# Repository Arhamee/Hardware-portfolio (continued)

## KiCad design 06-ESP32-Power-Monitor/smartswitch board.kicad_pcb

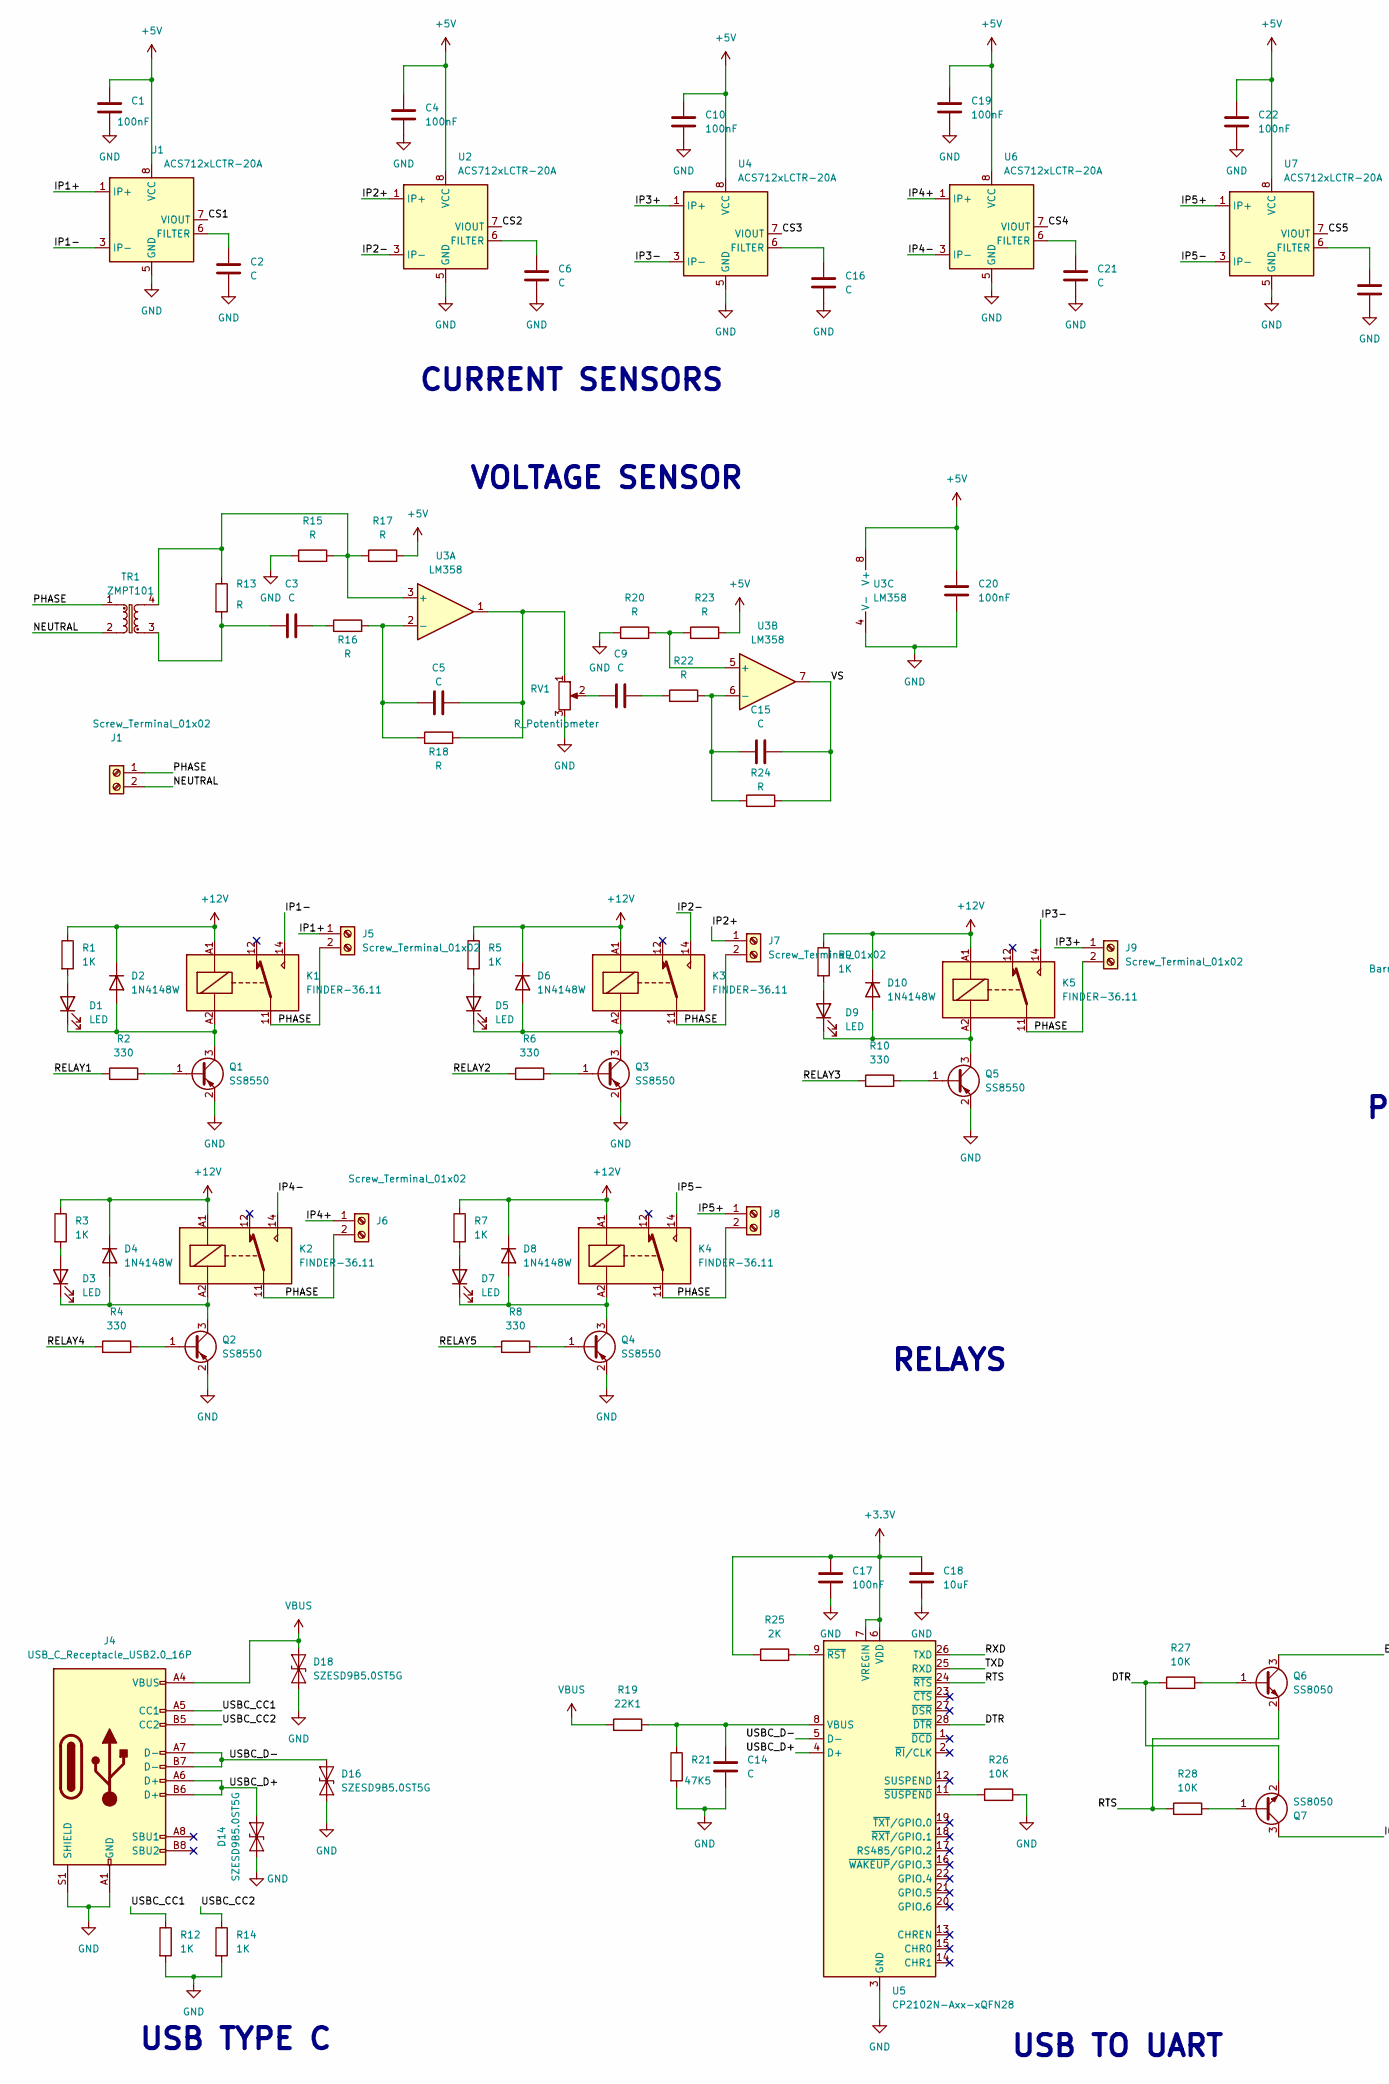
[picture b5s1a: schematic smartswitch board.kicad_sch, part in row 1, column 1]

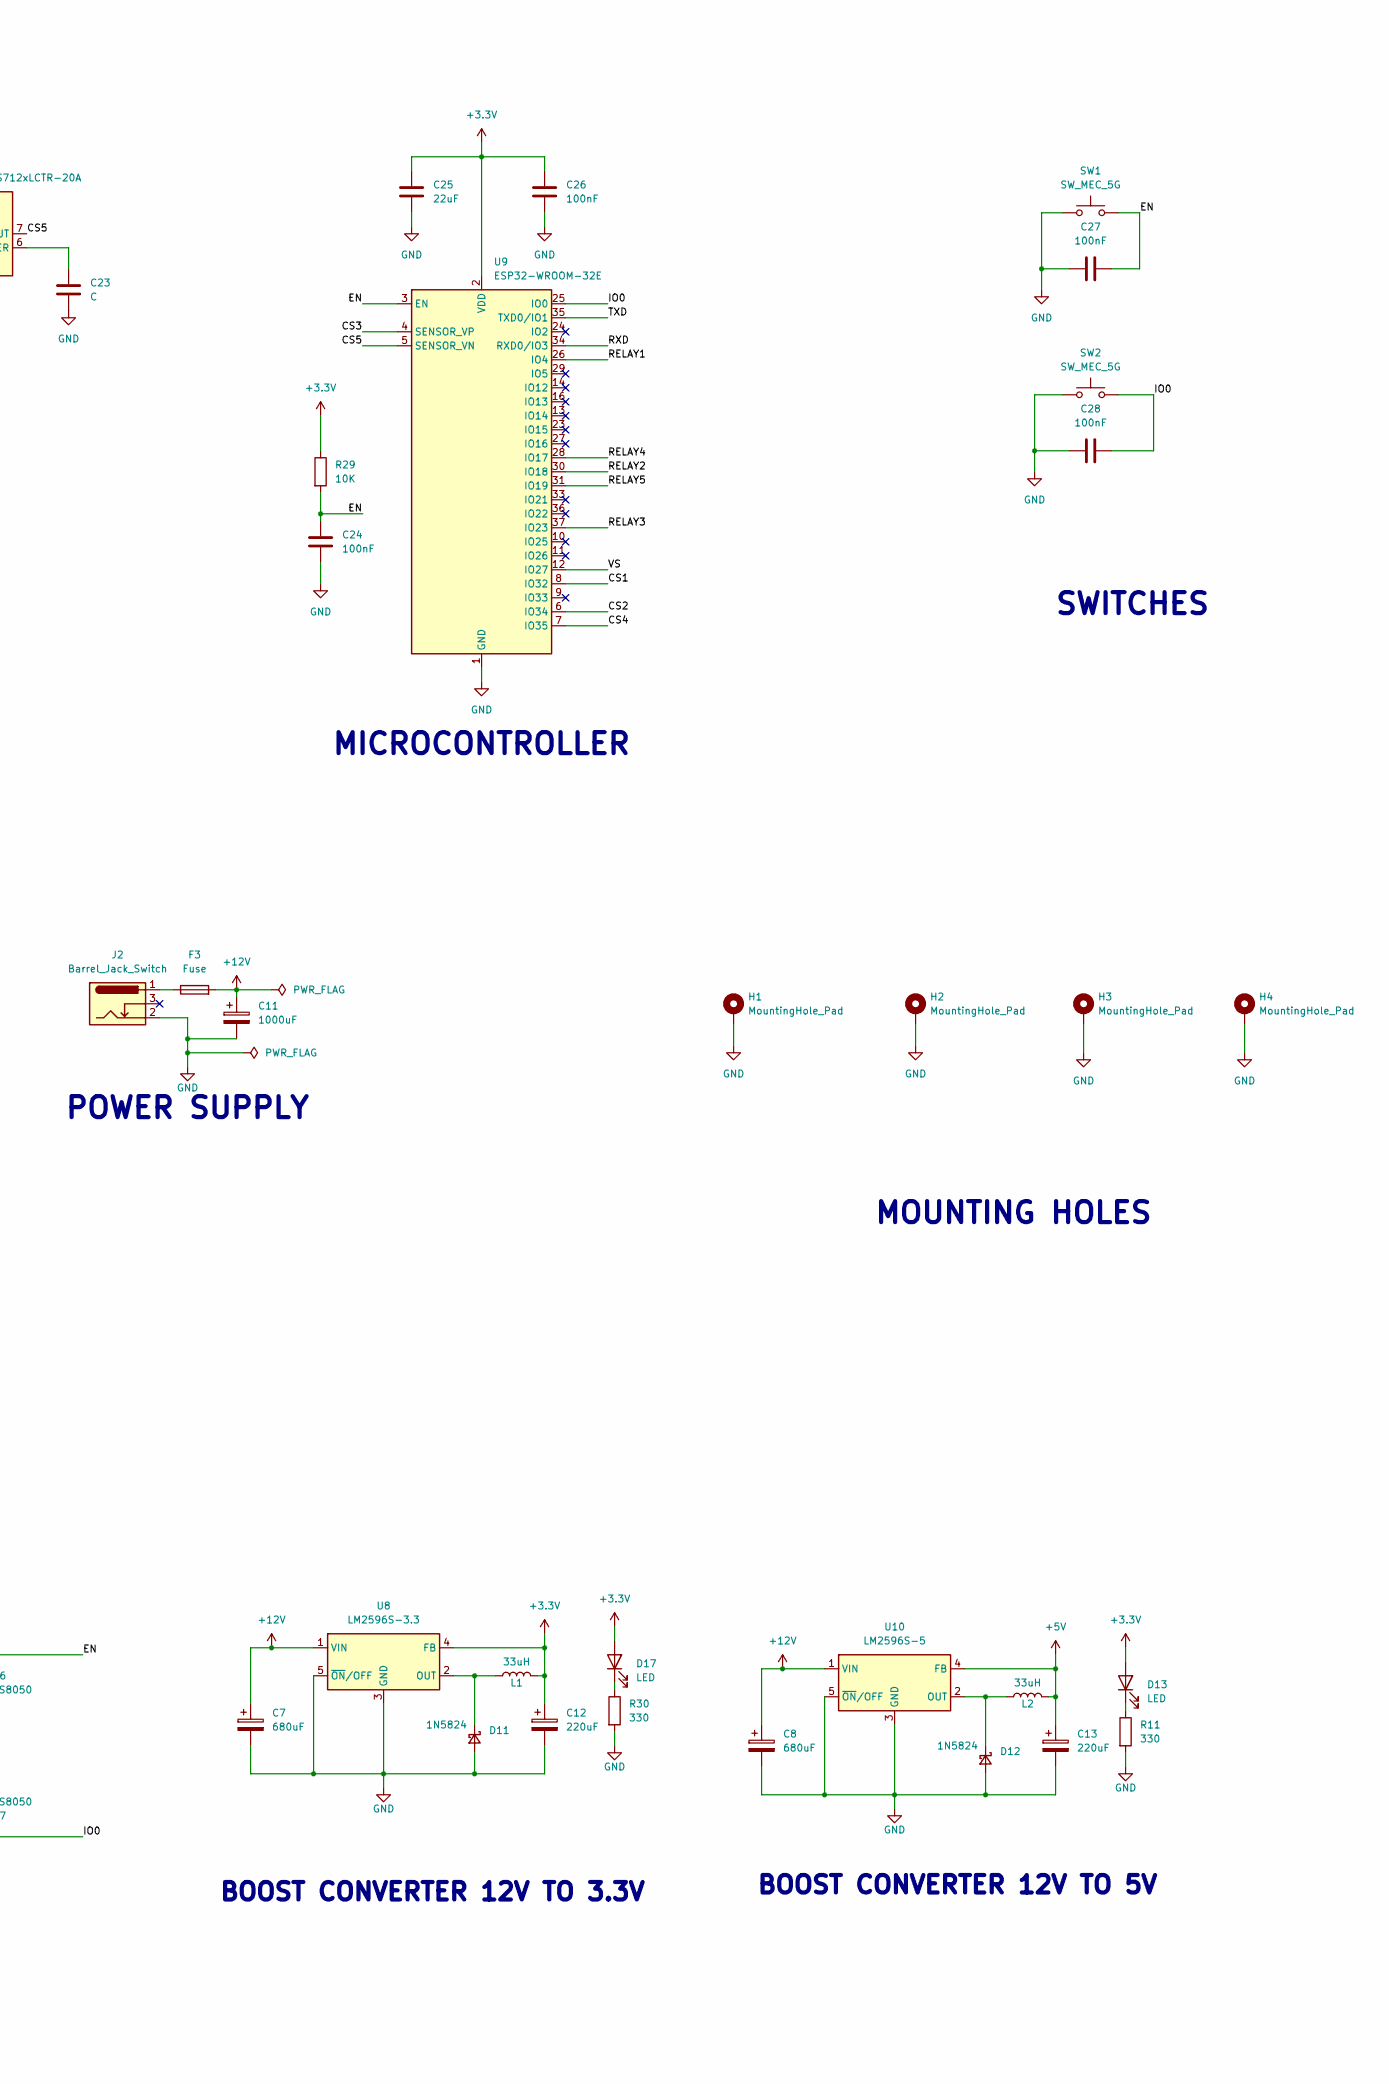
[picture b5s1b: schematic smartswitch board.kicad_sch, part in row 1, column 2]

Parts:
C1, C4, C10, C17, C19, C20, C22, C24, C26, C27, C28: 100nF; C_0402_1005Metric_Pad0.74x0.62mm_HandSolder
C2, C3, C5, C6, C9, C14, C15, C16, C23: C; C_0402_1005Metric_Pad0.74x0.62mm_HandSolder
C7, C8: 680uF; CP_Radial_D7.5mm_P2.50mm
C11: 1000uF; CP_Radial_D8.0mm_P3.50mm
C12, C13: 220uF; CP_Radial_D6.3mm_P2.50mm
C18: 10uF; C_0603_1608Metric_Pad1.08x0.95mm_HandSolder
C21: C; C_0603_1608Metric_Pad1.08x0.95mm_HandSolder
C25: 22uF; C_0603_1608Metric_Pad1.08x0.95mm_HandSolder
D1, D3, D5: LED; C_0402_1005Metric_Pad0.74x0.62mm_HandSolder
D2, D4, D6, D8, D10: 1N4148W; D_SOD-123
D7, D9, D13, D17: LED; LED_0402_1005Metric_Pad0.77x0.64mm_HandSolder
D11, D12: 1N5824; D_0603_1608Metric_Pad1.05x0.95mm_HandSolder
D14, D16, D18: SZESD9B5.0ST5G; D_SOD-923
F3: Fuse; Fuse_1210_3225Metric_Pad1.42x2.65mm_HandSolder
H1, H2, H3, H4: MountingHole_Pad; MountingHole_2.2mm_M2_DIN965_Pad
J1, J5, J6, J7, J8, J9: Screw_Terminal_01x02; TerminalBlock_Phoenix_MKDS-1,5-2_1x02_P5.00mm_Horizontal
J2: Barrel_Jack_Switch; BarrelJack_Horizontal
J4: USB_C_Receptacle_USB2.0_16P; USB_C_Receptacle_GCT_USB4105-xx-A_16P_TopMnt_Horizontal
K1, K2, K3, K4, K5: FINDER-36.11; Relay_SPDT_Finder_36.11
L1, L2: 33uH; L_Changjiang_FNR4015S
Q1, Q2, Q3, Q4, Q5: SS8550; SOT-23
Q6, Q7: SS8050; SOT-23
R1, R3, R5, R7, R9, R12, R14: 1K; R_0603_1608Metric_Pad0.98x0.95mm_HandSolder
R2, R4, R6, R8, R10, R11, R30: 330; R_0603_1608Metric_Pad0.98x0.95mm_HandSolder
R13, R15, R16, R17, R18, R20, R22, R23, R24: R; R_0603_1608Metric_Pad0.98x0.95mm_HandSolder
R19: 22K1; R_0603_1608Metric_Pad0.98x0.95mm_HandSolder
R21: 47K5; R_0603_1608Metric_Pad0.98x0.95mm_HandSolder
R25: 2K; R_0603_1608Metric_Pad0.98x0.95mm_HandSolder
R26, R27, R28, R29: 10K; R_0603_1608Metric_Pad0.98x0.95mm_HandSolder
RV1: R_Potentiometer; Potentiometer_Bourns_3296W_Vertical
SW1, SW2: SW_MEC_5G; PTS645S_SMTR92_CNK
TR1: ZMPT101; Transformer_Zeming_ZMPT101K
U1, U2, U4, U6, U7: ACS712xLCTR-20A; SOIC-8_3.9x4.9mm_P1.27mm
U3: LM358; SOIC-8_3.9x4.9mm_P1.27mm
U5: CP2102N-Axx-xQFN28; QFN-28-1EP_5x5mm_P0.5mm_EP3.35x3.35mm
U8: LM2596S-3.3; TO-263-5_TabPin3
U9: ESP32-WROOM-32E; ESP32-WROOM-32D
U10: LM2596S-5; TO-263-5_TabPin3

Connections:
+3.3V: C12.1, C17.1, C18.1, C25.1, C26.1, D13.2 (A), D17.2 (A), L1.2, R25.1, R29.1, U5.6 (VDD), U5.7 (VREGIN), U8.4 (FB), U9.2 (VDD)
+5V: C1.1, C4.1, C10.1, C13.1, C19.1, C20.2, C22.1, L2.2, R17.2, R23.2, U1.8 (VCC), U2.8 (VCC), U3.8 (V+), U4.8 (VCC), U6.8 (VCC), U7.8 (VCC), U10.4 (FB)
+12V: C7.1, C8.1, C11.1, D2.1 (K), D4.1 (K), D6.1 (K), D8.1 (K), D10.1 (K), F3.2, K1.A1, K2.A1, K3.A1, K4.A1, K5.A1, R1.1, R3.1, R5.1, R7.1, R9.1, U8.1 (VIN), U10.1 (VIN)
/CS1: U1.7 (VIOUT), U9.8 (IO32)
/CS2: U2.7 (VIOUT), U9.6 (IO34)
/CS3: U4.7 (VIOUT), U9.4 (SENSOR_VP)
/CS4: U6.7 (VIOUT), U9.7 (IO35)
/CS5: U7.7 (VIOUT), U9.5 (SENSOR_VN)
/DTR: Q7.2 (E), R27.1, U5.28 (~DTR)
/EN: C24.1, C27.1, Q6.3 (C), R29.2, SW1.3 (B), SW1.4 (B), U9.3 (EN)
/IO0: C28.2, Q7.3 (C), SW2.3 (B), SW2.4 (B), U9.25 (IO0)
/IP1+: J5.1, U1.1 (IP+), U1.2 (IP+)
/IP1-: K1.14, U1.3 (IP-), U1.4 (IP-)
/IP2+: J7.1, U2.1 (IP+), U2.2 (IP+)
/IP2-: K3.14, U2.3 (IP-), U2.4 (IP-)
/IP3+: J9.1, U4.1 (IP+), U4.2 (IP+)
/IP3-: K5.14, U4.3 (IP-), U4.4 (IP-)
/IP4+: J6.1, U6.1 (IP+), U6.2 (IP+)
/IP4-: K2.14, U6.3 (IP-), U6.4 (IP-)
/IP5+: J8.1, U7.1 (IP+), U7.2 (IP+)
/IP5-: K4.14, U7.3 (IP-), U7.4 (IP-)
/NEUTRAL: J1.2, TR1.2
/PHASE: J1.1, J5.2, J6.2, J7.2, J8.2, J9.2, K1.11, K2.11, K3.11, K4.11, K5.11, TR1.1
/RELAY1: R2.1, U9.26 (IO4)
/RELAY2: R6.1, U9.30 (IO18)
/RELAY3: R10.1, U9.37 (IO23)
/RELAY4: R4.1, U9.28 (IO17)
/RELAY5: R8.1, U9.31 (IO19)
/RTS: Q6.2 (E), R28.1, U5.24 (~RTS)
/RXD: U5.26 (TXD), U9.34 (RXD0/IO3)
/TXD: U5.25 (RXD), U9.35 (TXD0/IO1)
/USBC_CC1: J4.A5 (CC1), R12.1
/USBC_CC2: J4.B5 (CC2), R14.1
/USBC_D+: D14.2 (A2), J4.A6 (D+), J4.B6 (D+), U5.4 (D+)
/USBC_D-: D16.2 (A2), J4.A7 (D-), J4.B7 (D-), U5.5 (D-)
/VS: C15.2, R24.2, U3.7, U9.12 (IO27)
GND: C1.2, C2.2, C4.2, C6.2, C7.2, C8.2, C10.2, C11.2, C12.2, C13.2, C14.2, C16.2, C17.2, C18.2, C19.2, C20.1, C21.2, C22.2, C23.2, C24.2, C25.2, C26.2, C27.2, C28.1, D11.2 (A), D12.2 (A), D14.1 (A1), D16.1 (A1), D18.1 (A1), H1.1, H2.1, H3.1, H4.1, J2.2, J4.A1 (GND), J4.A12 (GND), J4.B1 (GND), J4.B12 (GND), J4.S1 (SHIELD), Q1.2 (E), Q2.2 (E), Q3.2 (E), Q4.2 (E), Q5.2 (E), R11.2, R12.2, R14.2, R15.1, R20.1, R21.2, R26.2, R30.2, RV1.3, SW1.1 (A), SW1.2 (A), SW2.1 (A), SW2.2 (A), U1.5 (GND), U2.5 (GND), U3.4 (V-), U4.5 (GND), U5.3 (GND), U5.29 (GND), U6.5 (GND), U7.5 (GND), U8.3 (GND), U8.5 (~ON/OFF), U9.1 (GND), U9.15 (GND), U9.38 (GND), U9.39 (GND), U10.3 (GND), U10.5 (~ON/OFF)
unnamed: C3.1, R13.2, TR1.3
unnamed: C3.2, R16.1
unnamed: C5.2, R18.2, RV1.1, U3.1
unnamed: C9.1, RV1.2
unnamed: C9.2, R22.1
unnamed: D1.2 (A), R1.2
unnamed: D1.1 (K), D2.2 (A), K1.A2, Q1.3 (C)
unnamed: D3.2 (A), R3.2
unnamed: D3.1 (K), D4.2 (A), K2.A2, Q2.3 (C)
unnamed: D5.2 (A), R5.2
unnamed: D5.1 (K), D6.2 (A), K3.A2, Q3.3 (C)
unnamed: D7.2 (A), R7.2
unnamed: D7.1 (K), D8.2 (A), K4.A2, Q4.3 (C)
unnamed: D9.2 (A), R9.2
unnamed: D9.1 (K), D10.2 (A), K5.A2, Q5.3 (C)
unnamed: D11.1 (K), L1.1, U8.2 (OUT)
unnamed: D12.1 (K), L2.1, U10.2 (OUT)
unnamed: D13.1 (K), R11.1
unnamed: D17.1 (K), R30.1
unnamed: F3.1, J2.1
unnamed: Q1.1 (B), R2.2
unnamed: Q2.1 (B), R4.2
unnamed: Q3.1 (B), R6.2
unnamed: Q4.1 (B), R8.2
unnamed: Q5.1 (B), R10.2
unnamed: Q6.1 (B), R27.2
unnamed: Q7.1 (B), R28.2
unnamed: C2.1, U1.6 (FILTER)
unnamed: C6.1, U2.6 (FILTER)
unnamed: R13.1, R15.2, R17.1, TR1.4, U3.3 (+)
unnamed: C5.1, R16.2, R18.1, U3.2 (-)
unnamed: R20.2, R23.1, U3.5 (+)
unnamed: C15.1, R22.2, R24.1, U3.6 (-)
unnamed: C16.1, U4.6 (FILTER)
unnamed: C14.1, R19.2, R21.1, U5.8 (VBUS)
unnamed: R25.2, U5.9 (~RST)
unnamed: R26.1, U5.11 (~SUSPEND)
unnamed: C21.1, U6.6 (FILTER)
unnamed: C23.1, U7.6 (FILTER)
VBUS: D18.2 (A2), J4.A4 (VBUS), J4.A9 (VBUS), J4.B4 (VBUS), J4.B9 (VBUS), R19.1

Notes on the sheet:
SWITCHES
USB TYPE C
USB TO UART
VOLTAGE SENSOR
POWER SUPPLY
CURRENT SENSORS
MICROCONTROLLER
RELAYS
BOOST CONVERTER 12V TO 3.3V
BOOST CONVERTER 12V TO 5V
MOUNTING HOLES

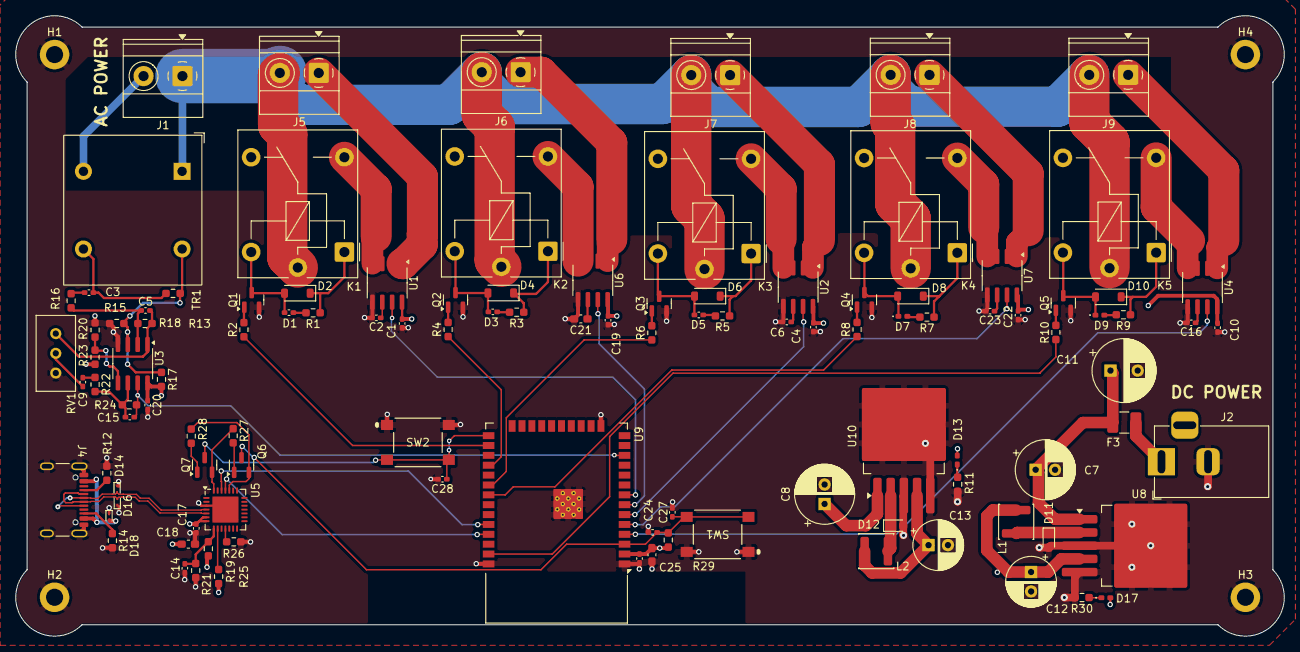
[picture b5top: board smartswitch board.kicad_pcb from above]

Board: 4 copper layers, 163.3 x 79.9 mm, 116 parts (0 on the bottom side), 77 nets.

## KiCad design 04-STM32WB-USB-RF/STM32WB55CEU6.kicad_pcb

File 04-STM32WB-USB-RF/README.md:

# STM32WB 4-Layer USB + RF Board

High-integrity 4-layer board combining USB 2.0 Full-Speed with 2.4 GHz RF,
built in KiCad 9.

**Status:** Design complete · DRC/ERC clean

## Stackup
| Layer | Purpose |
|---|---|
| 1 (Top) | Signal — components, USB D+/D−, RF traces |
| 2 | Solid ground plane |
| 3 | Second ground plane — low impedance, EMI shielding |
| 4 (Bottom) | 3.3V power plane, fed by single LDO |

The dual-ground stackup gives continuous return paths under high-speed traces,
reduces ground bounce and loop inductance, and sandwiches the power plane
between grounds.

## Features
- STM32WB dual-core (Cortex-M4 + Cortex-M0+)
- USB 2.0 FS with Type-C and ESD protection
- Impedance-controlled D+/D− (verified with KiCad 9 field solver)
- RF section: chip antenna + u.FL test point, routed over uninterrupted ground
- Via stitching, thermal reliefs, full DRC/ERC compliance

## What This Taught Me
Mixed-signal layout discipline — ground partitioning, return current paths, and
keeping sensitive RF away from switching noise.

Built following Phil Salmony's (Phil's Lab) PCB Design Course.

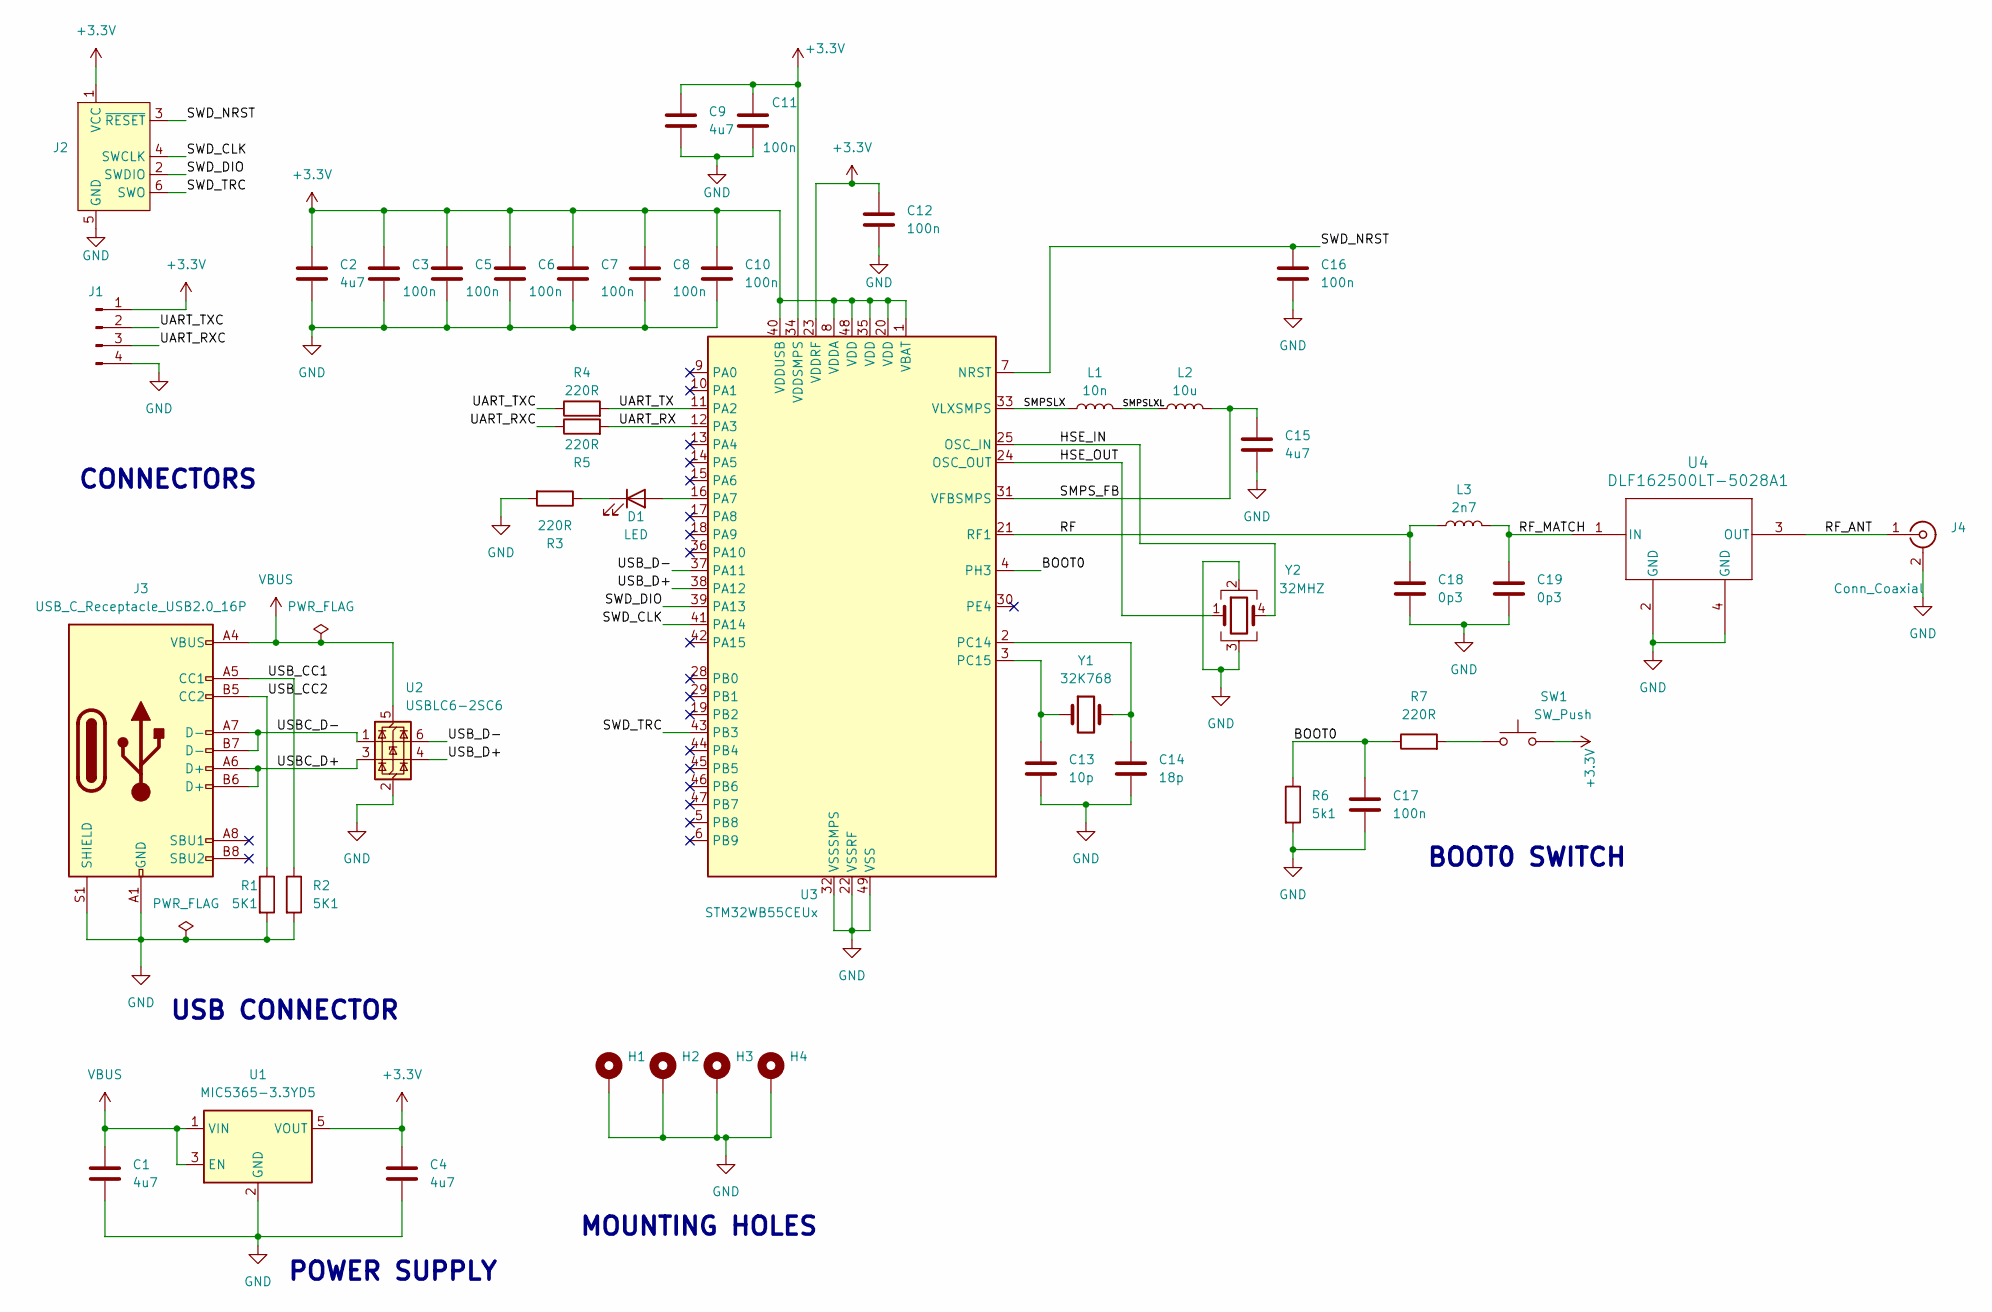
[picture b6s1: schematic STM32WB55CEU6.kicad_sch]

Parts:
C1, C2, C4, C9, C15: 4u7; C_0603_1608Metric_Pad1.08x0.95mm_HandSolder
C3, C5, C6, C7, C8, C10, C11, C12, C16, C17: 100n; C_0402_1005Metric_Pad0.74x0.62mm_HandSolder
C13: 10p; C_0402_1005Metric_Pad0.74x0.62mm_HandSolder
C14: 18p; C_0402_1005Metric_Pad0.74x0.62mm_HandSolder
C18, C19: 0p3; C_0402_1005Metric_Pad0.74x0.62mm_HandSolder
D1: LED; LED_0402_1005Metric_Pad0.77x0.64mm_HandSolder
H1, H2, H3, H4: MountingHole_Pad; MountingHole_2.2mm_M2_Pad
J1: Conn_01x04_Pin; Molex_PicoBlade_53048-0410_1x04_P1.25mm_Horizontal
J2: Conn_ARM_SWD_TagConnect_TC2030; Tag-Connect_TC2030-IDC-FP_2x03_P1.27mm_Vertical
J3: USB_C_Receptacle_USB2.0_16P; USB_C_Receptacle_GCT_USB4105-xx-A_16P_TopMnt_Horizontal
J4: Conn_Coaxial; U.FL_Hirose_U.FL-R-SMT-1_Vertical
L1: 10n; L_0402_1005Metric_Pad0.77x0.64mm_HandSolder
L2: 10u; L_0805_2012Metric_Pad1.05x1.20mm_HandSolder
L3: 2n7; L_0402_1005Metric_Pad0.77x0.64mm_HandSolder
R1, R2: 5K1; R_0402_1005Metric_Pad0.72x0.64mm_HandSolder
R3, R4, R5, R7: 220R; R_0402_1005Metric_Pad0.72x0.64mm_HandSolder
R6: 5k1; R_0402_1005Metric_Pad0.72x0.64mm_HandSolder
SW1: SW_Push; SW_SPST_CK_RS282G05A3
U1: MIC5365-3.3YD5; SOT-23-5
U2: USBLC6-2SC6; SOT-23-6
U3: STM32WB55CEUx; QFN-48-1EP_7x7mm_P0.5mm_EP5.6x5.6mm
U4: DLF162500LT-5028A1; DLF-4_1P6X0P8
Y1: 32K768; Crystal_SMD_2012-2Pin_2.0x1.2mm
Y2: 32MHZ; Crystal_SMD_2016-4Pin_2.0x1.6mm

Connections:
+3.3V: C2.1, C3.1, C4.1, C5.1, C6.1, C7.1, C8.1, C9.1, C10.1, C11.1, C12.1, J1.1, J2.1 (VCC), SW1.2, U1.5 (VOUT), U3.1 (VBAT), U3.8 (VDDA), U3.20 (VDD), U3.23 (VDDRF), U3.34 (VDDSMPS), U3.35 (VDD), U3.40 (VDDUSB), U3.48 (VDD)
/BOOT0: C17.1, R6.1, R7.1, U3.4 (PH3)
/HSE_IN: U3.25 (OSC_IN), Y2.4
/HSE_OUT: U3.24 (OSC_OUT), Y2.1
/RF: C18.1, L3.1, U3.21 (RF1)
/RF_ANT: J4.1 (In), U4.3 (OUT)
/RF_MATCH: C19.1, L3.2, U4.1 (IN)
/SMPSLX: L1.1, U3.33 (VLXSMPS)
/SMPSLXL: L1.2, L2.1
/SMPS_FB: C15.1, L2.2, U3.31 (VFBSMPS)
/SWD_CLK: J2.4 (SWCLK), U3.41 (PA14)
/SWD_DIO: J2.2 (SWDIO), U3.39 (PA13)
/SWD_NRST: C16.1, J2.3 (~RESET), U3.7 (NRST)
/SWD_TRC: J2.6 (SWO), U3.43 (PB3)
/UART_RX: R5.2, U3.12 (PA3)
/UART_RXC: J1.3, R5.1
/UART_TX: R4.2, U3.11 (PA2)
/UART_TXC: J1.2, R4.1
/USBC_D+: J3.A6 (D+), J3.B6 (D+), U2.3 (I/O2)
/USBC_D-: J3.A7 (D-), J3.B7 (D-), U2.1 (I/O1)
/USB_CC1: J3.A5 (CC1), R2.1
/USB_CC2: J3.B5 (CC2), R1.1
/USB_D+: U2.4 (I/O2), U3.38 (PA12)
/USB_D-: U2.6 (I/O1), U3.37 (PA11)
GND: C1.2, C2.2, C3.2, C4.2, C5.2, C6.2, C7.2, C8.2, C9.2, C10.2, C11.2, C12.2, C13.2, C14.2, C15.2, C16.2, C17.2, C18.2, C19.2, H1.1, H2.1, H3.1, H4.1, J1.4, J2.5 (GND), J3.A1 (GND), J3.A12 (GND), J3.B1 (GND), J3.B12 (GND), J3.S1 (SHIELD), J4.2 (Ext), R1.2, R2.2, R3.2, R6.2, U1.2 (GND), U2.2 (GND), U3.22 (VSSRF), U3.32 (VSSSMPS), U3.49 (VSS), U4.2 (GND), U4.4 (GND), Y2.2, Y2.3
unnamed: D1.2 (A), U3.16 (PA7)
unnamed: D1.1 (K), R3.1
unnamed: R7.2, SW1.1
unnamed: C14.1, U3.2 (PC14), Y1.2
unnamed: C13.1, U3.3 (PC15), Y1.1
VBUS: C1.1, J3.A4 (VBUS), J3.A9 (VBUS), J3.B4 (VBUS), J3.B9 (VBUS), U1.1 (VIN), U1.3 (EN), U2.5 (VBUS)

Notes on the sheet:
POWER SUPPLY
USB CONNECTOR
BOOT0 SWITCH
CONNECTORS
MOUNTING HOLES

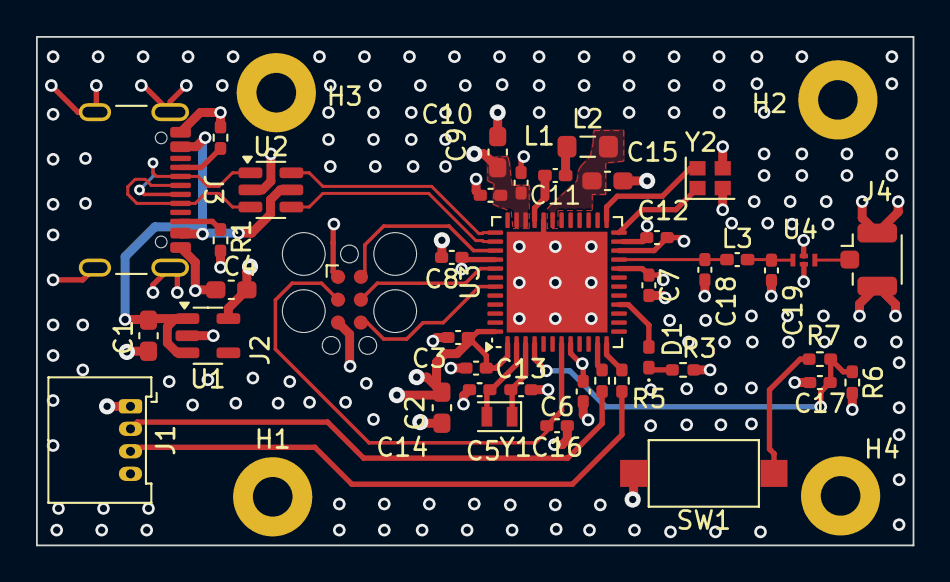
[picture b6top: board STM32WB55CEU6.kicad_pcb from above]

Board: 4 copper layers, 48.7 x 28.2 mm, 45 parts (0 on the bottom side), 31 nets.
